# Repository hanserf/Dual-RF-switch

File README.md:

# Dual-RF-switch

Like most stuff in life, 97% complete.
Based on evaluation board from datasheet.

Not produced, waiting for availability of components.

4 Layer stackup based for fabrication by JLPCB.
Recommend to remove vias in pads, or it will be hell to solder without a hot plate.
4 layer is chosen, but not needed. Will make trace width approx equal to smd component footprints.
All lines quite matched.
First design i Eagle, so probably some wtfs?

Coplanar waveguide calculations from:

http://wcalc.sourceforge.net/cgi-bin/coplanar.cgi?wc_unit_menu_1_0=nH&wc_unit_menu_1_1=inch&wc_unit_menu_2_0=mOhm&wc_unit_menu_2_1=inch&wc_unit_menu_3_0=pF&wc_unit_menu_3_1=inch&wc_unit_menu_4_0=uMho&wc_unit_menu_4_1=inch&wc_unit_menu_7_0=dB&wc_unit_menu_8_0=dB&wc_unit_menu_8_1=inch&wc_unit_menu_12_0=mil&wc_unit_menu_11_0=ns&wc_unit_menu_13_0=inch&w=0.34761&wc_unit_menu_0_0=mm&s=0.2&l=1.63549e%2B07&wc_unit_menu_5_0=nm&tmet=0.035&rho=3e-08&wc_unit_menu_9_0=Ohm&wc_unit_menu_9_1=m&rough=0.001&wc_unit_menu_10_0=mil&h=0.2&es=4.6&tand=0.01&freq=1.0&wc_unit_menu_6_0=GHz&analyze=Analyze&withgnd=on&Ro=50&elen=67.7599

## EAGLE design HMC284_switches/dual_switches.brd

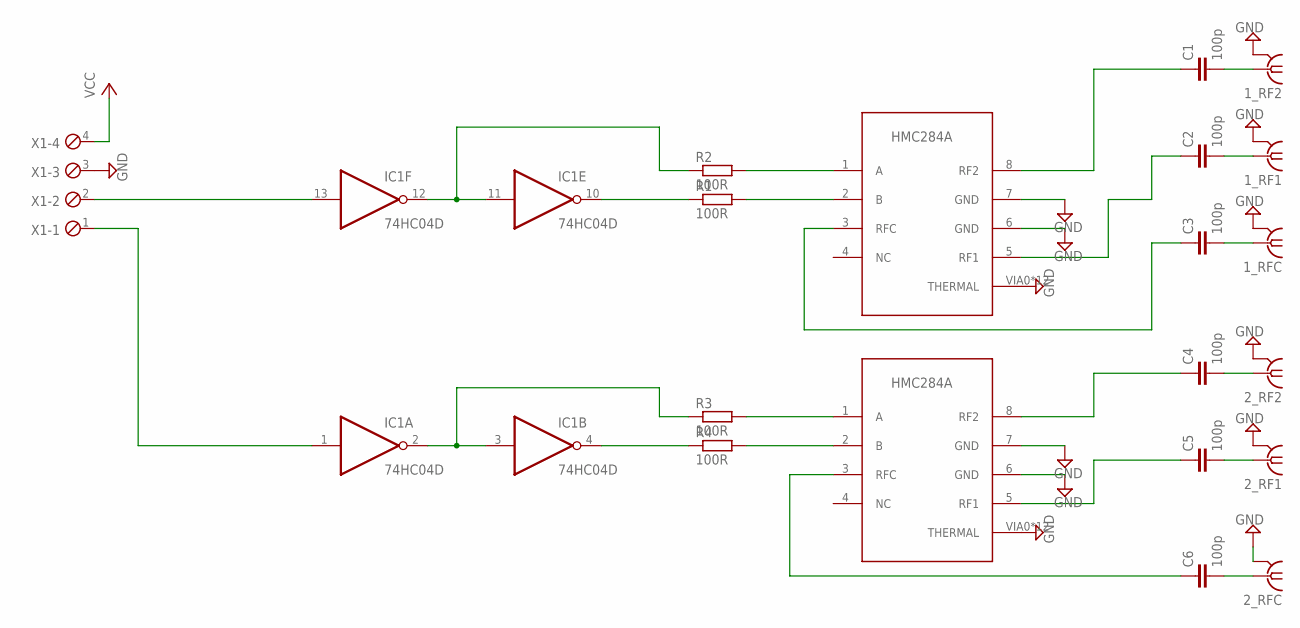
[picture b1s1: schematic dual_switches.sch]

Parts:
1_RF1, 1_RF2, 1_RFC, 2_RF1, 2_RF2, 2_RFC: SMA-142-0701-801/806; J502-ND-142-0701-801/806
C1, C2, C3, C4, C5, C6: 100p; C0402
IC1: 74HC04D; SO14
R1, R2, R3, R4: 100R; R0603
U$1, U$2: HMC284A; MSOP-8G
X1: MPT4; 4POL254

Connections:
GND: 1_RF1.G@1 (2), 1_RF1.G@2 (2), 1_RF1.G@3 (2), 1_RF1.G@4 (2), 1_RF2.G@1 (2), 1_RF2.G@2 (2), 1_RF2.G@3 (2), 1_RF2.G@4 (2), 1_RFC.G@1 (2), 1_RFC.G@2 (2), 1_RFC.G@3 (2), 1_RFC.G@4 (2), 2_RF1.G@1 (2), 2_RF1.G@2 (2), 2_RF1.G@3 (2), 2_RF1.G@4 (2), 2_RF2.G@1 (2), 2_RF2.G@2 (2), 2_RF2.G@3 (2), 2_RF2.G@4 (2), 2_RFC.G@1 (2), 2_RFC.G@2 (2), 2_RFC.G@3 (2), 2_RFC.G@4 (2), IC1.7 (GND), U$1.6 (GND), U$1.7 (GND), U$1.VIA0 (THERMAL), U$1.VIA1 (THERMAL), U$1.VIA2 (THERMAL), U$1.VIA3 (THERMAL), U$1.VIA5 (THERMAL), U$1.VIA6 (THERMAL), U$1.VIA7 (THERMAL), U$1.VIA8 (THERMAL), U$1.VIA9 (THERMAL), U$1.VIA10 (THERMAL), U$1.VIA11 (THERMAL), U$1.VIA12 (THERMAL), U$2.6 (GND), U$2.7 (GND), U$2.VIA0 (THERMAL), U$2.VIA1 (THERMAL), U$2.VIA2 (THERMAL), U$2.VIA3 (THERMAL), U$2.VIA5 (THERMAL), U$2.VIA6 (THERMAL), U$2.VIA7 (THERMAL), U$2.VIA8 (THERMAL), U$2.VIA9 (THERMAL), U$2.VIA10 (THERMAL), U$2.VIA11 (THERMAL), U$2.VIA12 (THERMAL), X1.3
unnamed: IC1.13 (I), X1.2
unnamed: IC1.11 (I), IC1.12 (O), R2.1
unnamed: IC1.2 (O), IC1.3 (I), R3.1
unnamed: R1.2, U$1.2 (B)
unnamed: C1.1, U$1.8 (RF2)
unnamed: IC1.1 (I), X1.1
unnamed: IC1.10 (O), R1.1
unnamed: C3.1, U$1.3 (RFC)
unnamed: C2.1, U$1.5 (RF1)
unnamed: C4.1, U$2.8 (RF2)
unnamed: C5.1, U$2.5 (RF1)
unnamed: C6.1, U$2.3 (RFC)
unnamed: R2.2, U$1.1 (A)
unnamed: R3.2, U$2.1 (A)
unnamed: R4.2, U$2.2 (B)
unnamed: 2_RF1.1, C5.2
unnamed: 2_RFC.1, C6.2
unnamed: 2_RF2.1, C4.2
unnamed: 1_RFC.1, C3.2
unnamed: 1_RF1.1, C2.2
unnamed: 1_RF2.1, C1.2
unnamed: IC1.4 (O), R4.1
VCC: IC1.14 (VCC), X1.4

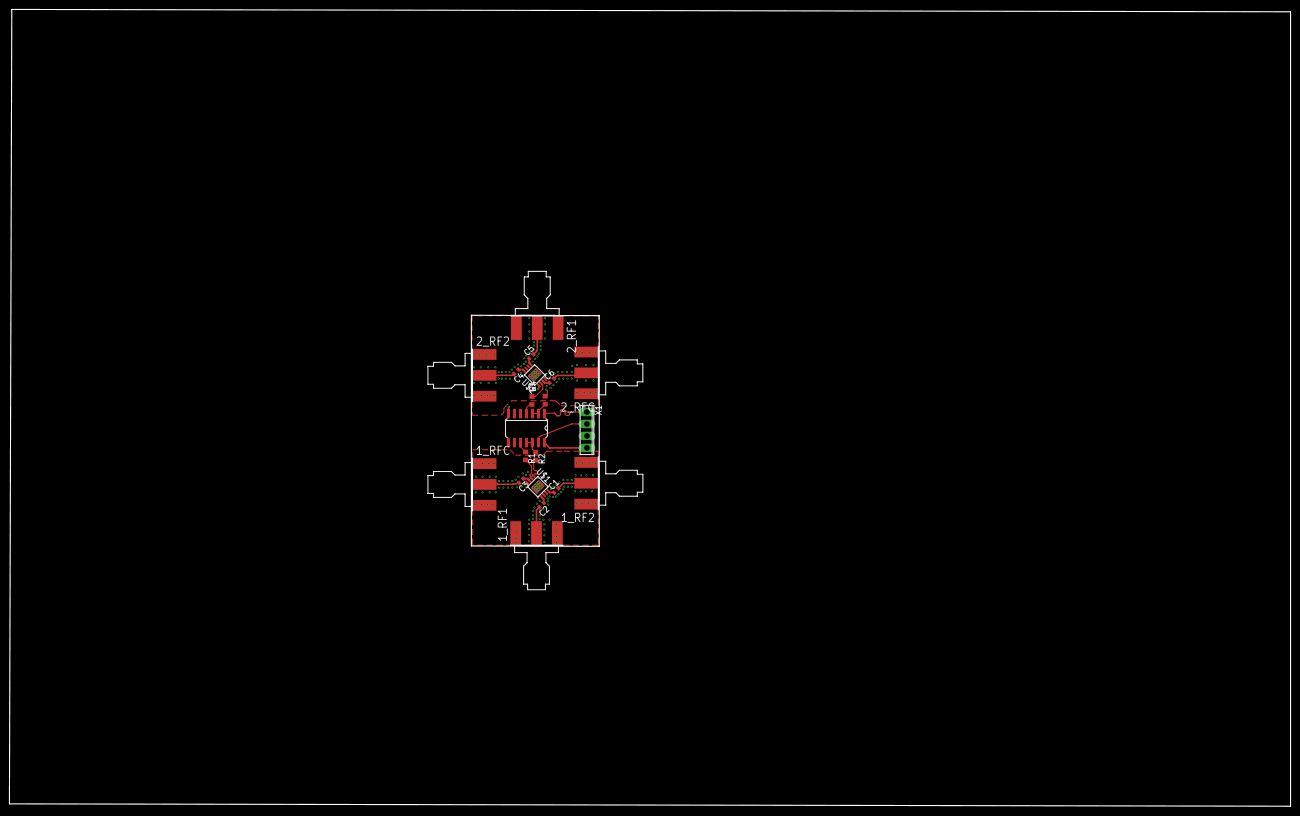
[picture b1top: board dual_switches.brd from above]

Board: 4 copper layers, 271.6 x 168.9 mm, 20 parts (0 on the bottom side), 24 nets.

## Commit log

2019-05-07 First Push, 97%er
2019-05-07 added layout image
2019-05-08 Added datasheet
